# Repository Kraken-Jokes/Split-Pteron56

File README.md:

# Split-Pteron56
Split version of the Pteron56+ encoder
*UNTESTED AND IN THE WORKS*

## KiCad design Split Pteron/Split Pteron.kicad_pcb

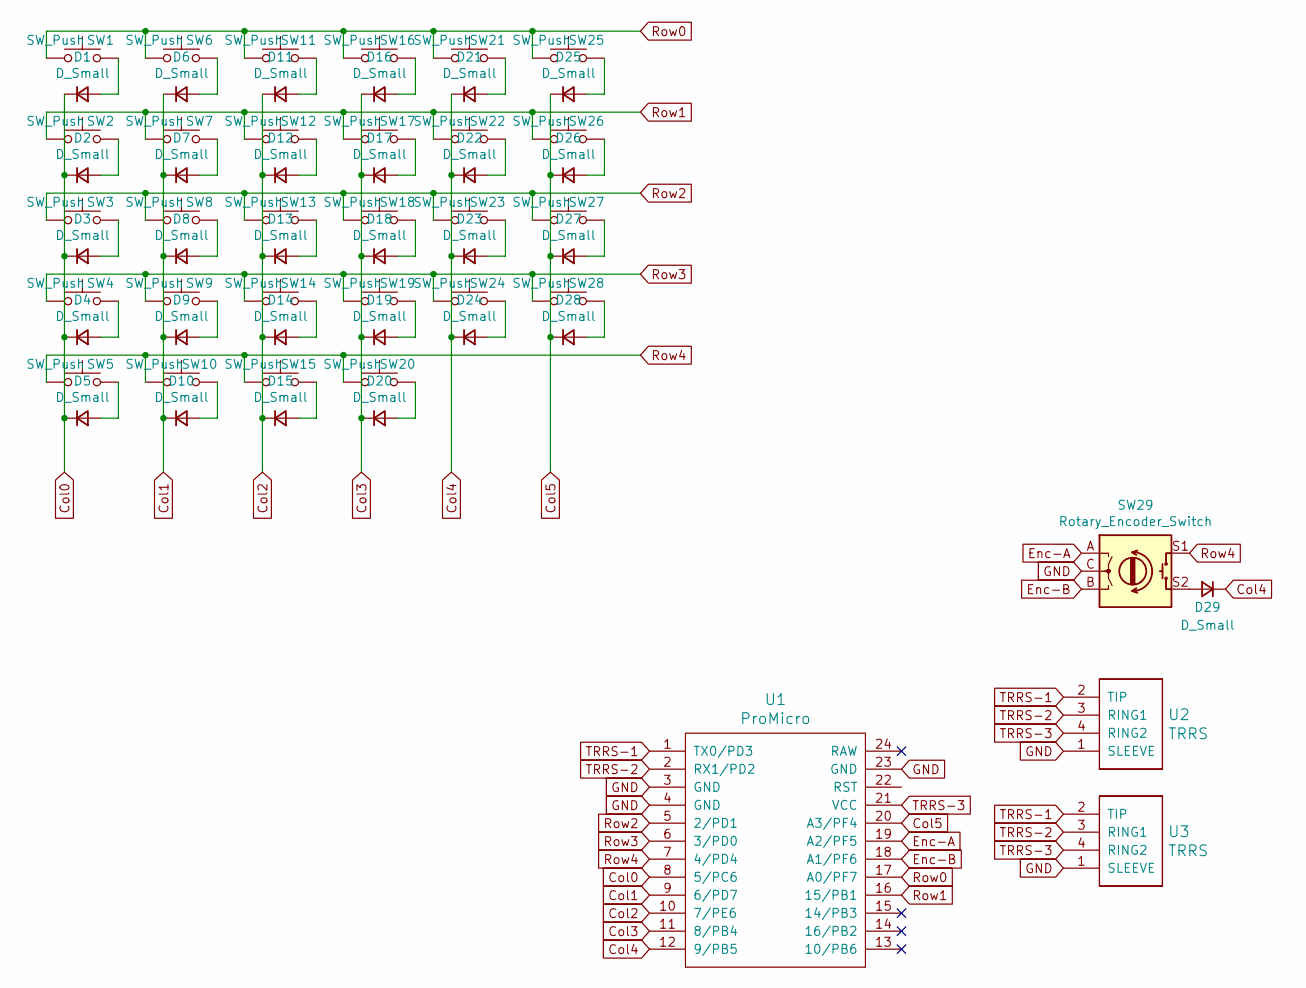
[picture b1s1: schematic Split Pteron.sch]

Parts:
D1, D2, D3, D4, D5, D6, D7, D8, D9, D10, D11, D12, D13, D14, D15, D16, D17, D18, D19, D20, D21, D22, D23, D24, D25, D26, D27, D28, D29: D_Small; D_DO-35_SOD27_P7.62mm_Horizontal
SW1, SW2, SW3, SW4, SW5, SW6, SW7, SW8, SW9, SW10, SW11, SW12, SW13, SW14, SW15, SW16, SW17, SW18, SW19, SW20, SW21, SW22, SW23, SW24, SW25, SW26, SW27, SW28: SW_Push; SW_MX_reversible
SW29: Rotary_Encoder_Switch; RotaryEncoder_EC11
U1: ProMicro; Pro_Micro
U2, U3: TRRS; Jack_3.5mm_PJ320E_Horizontal

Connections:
Col0: D1.1 (K), D2.1 (K), D3.1 (K), D4.1 (K), D5.1 (K), U1.8 (5/PC6)
Col1: D6.1 (K), D7.1 (K), D8.1 (K), D9.1 (K), D10.1 (K), U1.9 (6/PD7)
Col2: D11.1 (K), D12.1 (K), D13.1 (K), D14.1 (K), D15.1 (K), U1.10 (7/PE6)
Col3: D16.1 (K), D17.1 (K), D18.1 (K), D19.1 (K), D20.1 (K), U1.11 (8/PB4)
Col4: D21.1 (K), D22.1 (K), D23.1 (K), D24.1 (K), D29.1 (K), U1.12 (9/PB5)
Col5: D25.1 (K), D26.1 (K), D27.1 (K), D28.1 (K), U1.20 (A3/PF4)
Enc-A: SW29.A, U1.19 (A2/PF5)
Enc-B: SW29.B, U1.18 (A1/PF6)
GND: SW29.C, U1.3 (GND), U1.4 (GND), U1.23 (GND), U2.1 (SLEEVE), U3.1 (SLEEVE)
unnamed: D1.2 (A), SW1.2
unnamed: D2.2 (A), SW2.2
unnamed: D3.2 (A), SW3.2
unnamed: D4.2 (A), SW4.2
unnamed: D5.2 (A), SW5.2
unnamed: D6.2 (A), SW6.2
unnamed: D7.2 (A), SW7.2
unnamed: D8.2 (A), SW8.2
unnamed: D9.2 (A), SW9.2
unnamed: D10.2 (A), SW10.2
unnamed: D11.2 (A), SW11.2
unnamed: D12.2 (A), SW12.2
unnamed: D13.2 (A), SW13.2
unnamed: D14.2 (A), SW14.2
unnamed: D15.2 (A), SW15.2
unnamed: D16.2 (A), SW16.2
unnamed: D17.2 (A), SW17.2
unnamed: D18.2 (A), SW18.2
unnamed: D19.2 (A), SW19.2
unnamed: D20.2 (A), SW20.2
unnamed: D21.2 (A), SW21.2
unnamed: D22.2 (A), SW22.2
unnamed: D23.2 (A), SW23.2
unnamed: D24.2 (A), SW24.2
unnamed: D25.2 (A), SW25.2
unnamed: D26.2 (A), SW26.2
unnamed: D27.2 (A), SW27.2
unnamed: D28.2 (A), SW28.2
unnamed: D29.2 (A), SW29.S2
Row0: SW1.1, SW6.1, SW11.1, SW16.1, SW21.1, SW25.1, U1.17 (A0/PF7)
Row1: SW2.1, SW7.1, SW12.1, SW17.1, SW22.1, SW26.1, U1.16 (15/PB1)
Row2: SW3.1, SW8.1, SW13.1, SW18.1, SW23.1, SW27.1, U1.5 (2/PD1)
Row3: SW4.1, SW9.1, SW14.1, SW19.1, SW24.1, SW28.1, U1.6 (3/PD0)
Row4: SW5.1, SW10.1, SW15.1, SW20.1, SW29.S1, U1.7 (4/PD4)
TRRS-1: U1.1 (TX0/PD3), U2.2 (TIP), U3.2 (TIP)
TRRS-2: U1.2 (RX1/PD2), U2.3 (RING1), U3.3 (RING1)
TRRS-3: U1.21 (VCC), U2.4 (RING2), U3.4 (RING2)

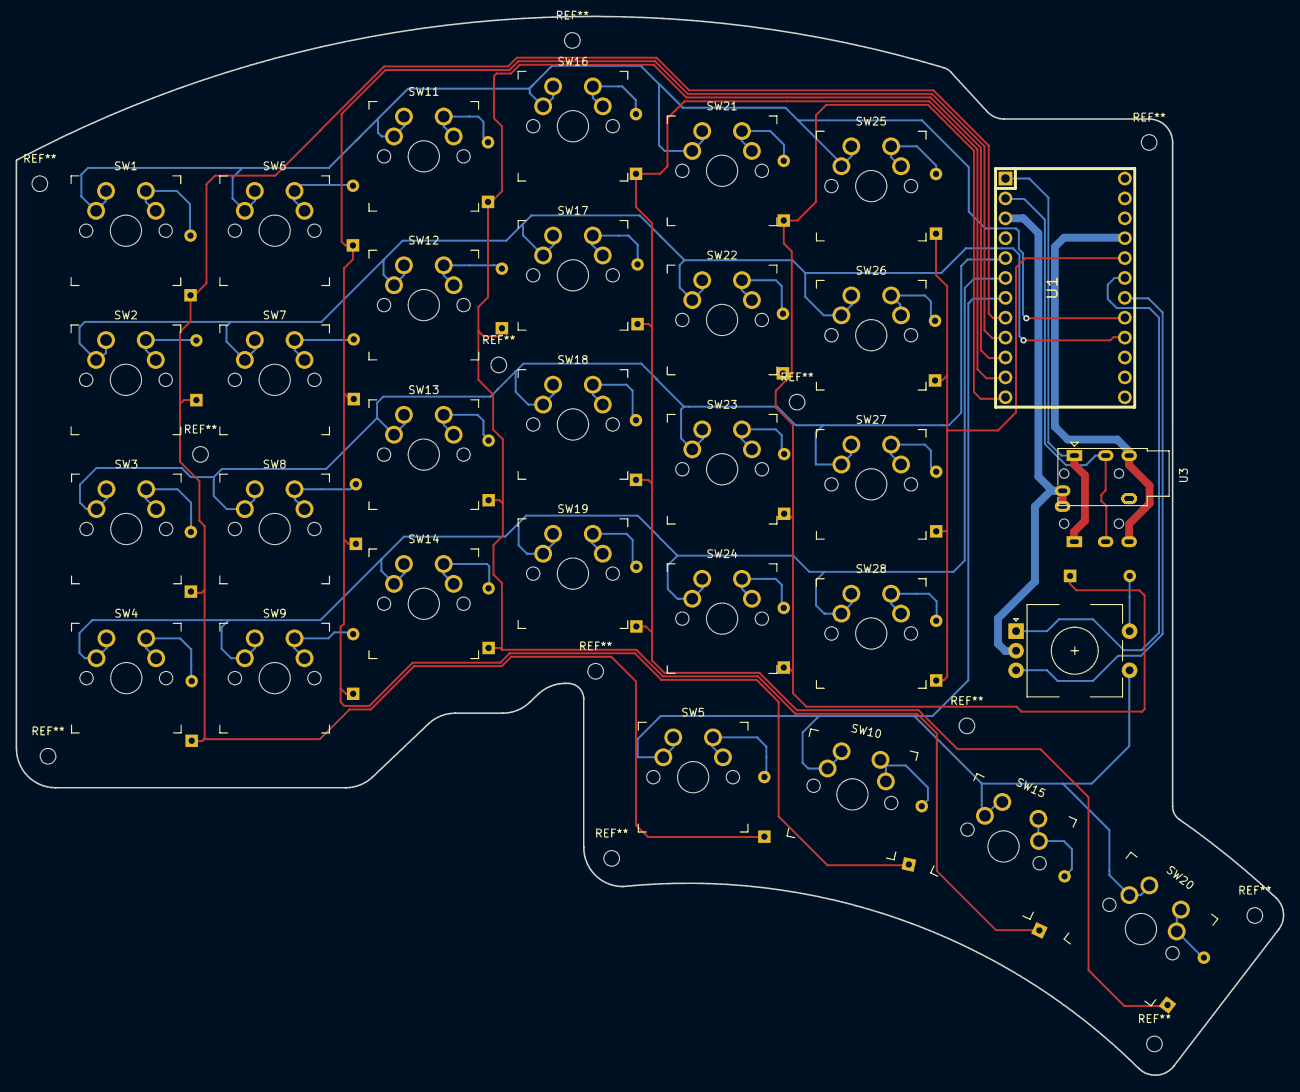
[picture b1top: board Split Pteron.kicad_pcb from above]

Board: 2 copper layers, 161.9 x 135.2 mm, 61 parts (1 on the bottom side), 46 nets.
